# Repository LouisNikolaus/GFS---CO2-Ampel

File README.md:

# CO2-Ampel mit D1 mini (ESP8266)

Trägerplatine 100 × 60 mm (2 Lagen, nur THT-Bauteile) + 3D-gedrucktes Gehäuse 105 × 65 × 27 mm.

## Ordner

```
Platine/        KiCad-10-Projekt (CO2-Ampel.kicad_pro hier öffnen)
  lib/          Projektbibliothek: Symbol + Footprint D1 mini
  fertigung/    Gerber-ZIP, Stückliste, Layout-PDF, Renderings
  pruefberichte/  ERC/DRC-Berichte
  scripts/      Generatoren für Schaltplan, Platine und Router
gehaeuse/       STL-Dateien für den 3D-Druck
  scripts/      Gehäuse-Generator (parametrisch)
ESP-Code/       Firmware für den D1 mini (folgt)
```

| Datei | Inhalt |
|---|---|
| `Platine/CO2-Ampel_Schaltplan.pdf` | Schaltplan zum Ansehen ohne KiCad |
| `Platine/fertigung/CO2-Ampel_Gerber.zip` | Gerber + Bohrdaten für JLCPCB / Aisler / PCBWay |
| `Platine/fertigung/Stueckliste.csv` | Stückliste |
| `gehaeuse/Unterschale.stl`, `gehaeuse/Deckel.stl` | Druckdateien (Deckel liegt schon richtig herum) |

## Belegung D1 mini

| Pin | Funktion |
|---|---|
| D1 (GPIO5) | I2C SCL (Display + Sensor) |
| D2 (GPIO4) | I2C SDA |
| D3 (GPIO0) | Taster gegen GND (interner Pull-up) |
| D5 / D6 / D7 | LED rot / gelb / grün |
| D8 (GPIO15) | Summer über BC547 |
| 5V / 3V3 / G | Versorgung (über USB des D1 mini) |

## Zusätzlich zur Stückliste

- 2 × Buchsenleiste 1×8, RM 2,54 (für den D1 mini)
- 4 × Schraube M3 × 8 (Platine auf Abstandshalter, selbstschneidend)
- Aktiver Summer 5 V, 12 mm, Rastermaß 7,6 mm
- Taster 6 × 6 mm mit **13 mm Bauhöhe**

## Vor der Bestellung prüfen

1. **Pinfolge des CO2-Sensors**: J2 ist VCC–GND–SCL–SDA belegt. Das Sensormodul (SCD40/SCD41/SCD30 …) vergleichen.
2. **Pinfolge des OLED**: J1 ist GND–VCC–SCL–SDA belegt. Manche Displays haben VCC–GND!
3. **JP1** (Lötbrücke): ab Werk 3,3 V für den Sensor. Für 5 V die Brücke 1-2 auftrennen und 2-3 verbinden.
4. **R1/R2** nur bestücken, wenn weder Display noch Sensor eigene Pull-ups haben.

## Gehäuse

- Material: PETG oder PLA, 0,2 mm Schichthöhe, keine Stützstrukturen nötig.
- Unterschale mit der Öffnung nach oben drucken, den Deckel mit der Sichtseite aufs Druckbett.
- Der Deckel wird nur gesteckt (Klemmrand). Wenn er zu stramm sitzt, in `gehaeuse/scripts/gen_case.py` den Wert `LIP_CLEAR` erhöhen.
- Die **Trennwand** im Deckel sitzt über dem Schlitz in der Platine. Sie trennt den Sensor thermisch vom warmen ESP8266 und verbessert so die Temperaturmessung.
- **LEDs** erst einlöten, wenn der Deckel aufgesetzt ist. So stecken sie genau in den Löchern.
- **Wichtig:** Die Bauhöhe hängt davon ab, wie D1 mini und Display gesteckt sind. Maßgeblich ist der Parameter `PARTS_H` (Standard 16 mm über Platinenoberseite). Nachmessen und bei Bedarf anpassen:
  `python gehaeuse/scripts/gen_case.py`

## Neu erzeugen

Alle Befehle im Hauptordner ausführen (normales Python braucht `pip install manifold3d numpy`):

```
python Platine/scripts/gen_lib.py
python Platine/scripts/gen_sch.py
kicad-cli sch export netlist --format kicadsexpr -o Platine/CO2-Ampel.net Platine/CO2-Ampel.kicad_sch
"C:\Program Files\KiCad\10.0\bin\python.exe" Platine/scripts/gen_pcb.py
"C:\Program Files\KiCad\10.0\bin\python.exe" Platine/scripts/route_pcb.py
python gehaeuse/scripts/gen_case.py
```

Achtung: `gen_pcb.py` und `route_pcb.py` überschreiben die Platine. Wer das Layout von Hand in KiCad weiterbearbeitet, führt die Skripte danach nicht mehr aus.

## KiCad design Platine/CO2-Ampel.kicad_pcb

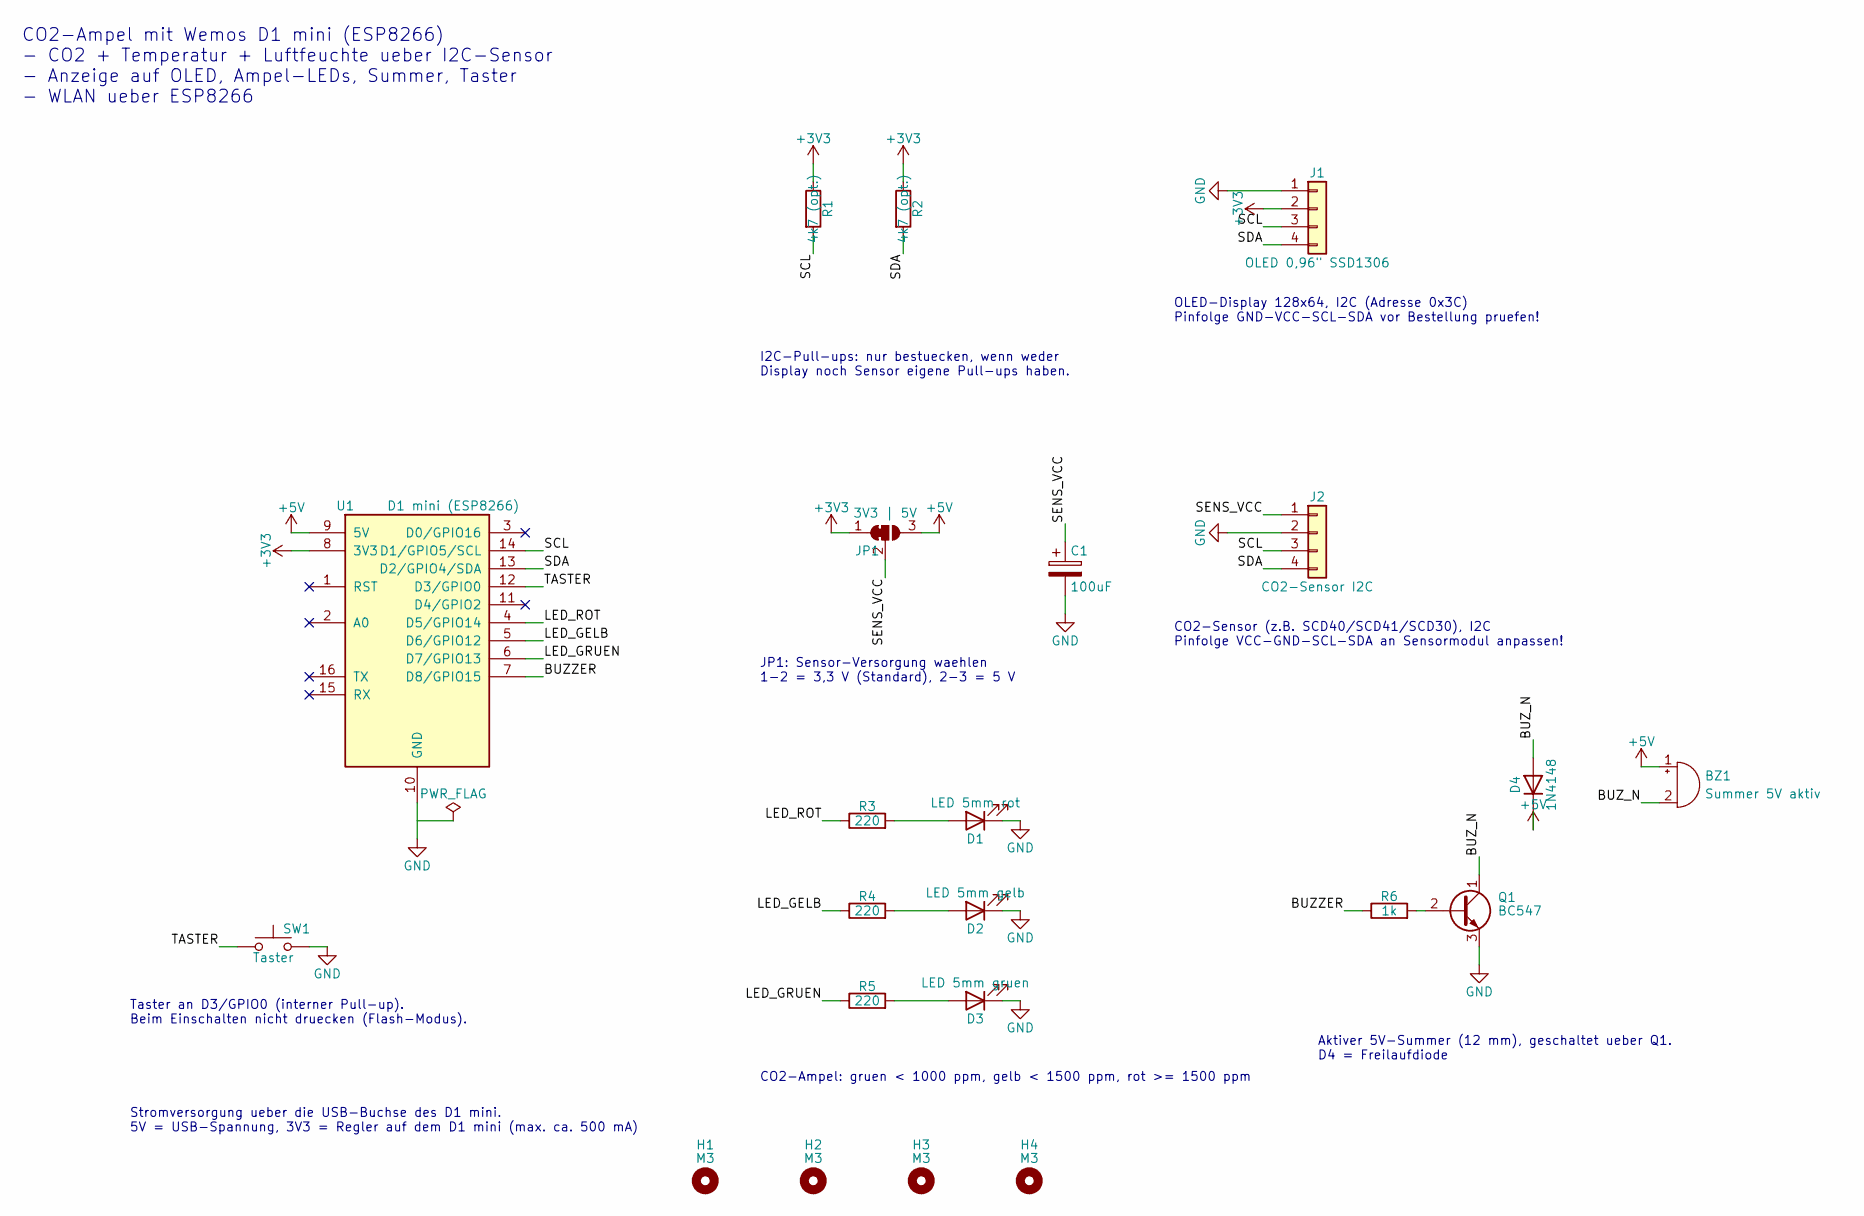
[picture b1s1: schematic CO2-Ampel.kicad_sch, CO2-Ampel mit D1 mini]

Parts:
BZ1: Summer 5V aktiv; Buzzer_12x9.5RM7.6
C1: 100uF; CP_Radial_D6.3mm_P2.50mm
D1: LED 5mm rot; LED_D5.0mm
D2: LED 5mm gelb; LED_D5.0mm
D3: LED 5mm gruen; LED_D5.0mm
D4: 1N4148; D_DO-35_SOD27_P7.62mm_Horizontal
H1, H2, H3, H4: M3; MountingHole_3.2mm_M3
J1: OLED 0,96" SSD1306; PinSocket_1x04_P2.54mm_Vertical
J2: CO2-Sensor I2C; PinSocket_1x04_P2.54mm_Vertical
JP1: 3V3 | 5V; SolderJumper-3_P1.3mm_Bridged12_RoundedPad1.0x1.5mm_NumberL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
Q1: BC547; TO-92_Inline
R1, R2: 4k7 (opt.); R_Axial_DIN0207_L6.3mm_D2.5mm_P7.62mm_Horizontal
R3, R4, R5: 220; R_Axial_DIN0207_L6.3mm_D2.5mm_P7.62mm_Horizontal
R6: 1k; R_Axial_DIN0207_L6.3mm_D2.5mm_P7.62mm_Horizontal
SW1: Taster; SW_PUSH_6mm_H13mm
U1: D1 mini (ESP8266); WEMOS_D1_mini

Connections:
+3V3: J1.2, JP1.1 (A), R1.1, R2.1, U1.8 (3V3)
+5V: BZ1.1 (+), D4.1 (K), JP1.3 (B), U1.9 (5V)
/BUZZER: R6.1, U1.7 (D8/GPIO15)
/BUZ_N: BZ1.2 (-), D4.2 (A), Q1.1 (C)
/LED_GELB: R4.1, U1.5 (D6/GPIO12)
/LED_GRUEN: R5.1, U1.6 (D7/GPIO13)
/LED_ROT: R3.1, U1.4 (D5/GPIO14)
/SCL: J1.3, J2.3, R1.2, U1.14 (D1/GPIO5/SCL)
/SDA: J1.4, J2.4, R2.2, U1.13 (D2/GPIO4/SDA)
/SENS_VCC: C1.1, J2.1, JP1.2 (C)
/TASTER: SW1.1, U1.12 (D3/GPIO0)
GND: C1.2, D1.1 (K), D2.1 (K), D3.1 (K), J1.1, J2.2, Q1.3 (E), SW1.2, U1.10 (GND)
unnamed: D1.2 (A), R3.2
unnamed: D2.2 (A), R4.2
unnamed: D3.2 (A), R5.2
unnamed: Q1.2 (B), R6.2

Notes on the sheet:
Stromversorgung ueber die USB-Buchse des D1 mini. 5V = USB-Spannung, 3V3 = Regler auf dem D1 mini (max. ca. 500 mA)
I2C-Pull-ups: nur bestuecken, wenn weder Display noch Sensor eigene Pull-ups haben.
OLED-Display 128x64, I2C (Adresse 0x3C) Pinfolge GND-VCC-SCL-SDA vor Bestellung pruefen!
CO2-Sensor (z.B. SCD40/SCD41/SCD30), I2C Pinfolge VCC-GND-SCL-SDA an Sensormodul anpassen!
JP1: Sensor-Versorgung waehlen 1-2 = 3,3 V (Standard), 2-3 = 5 V
CO2-Ampel: gruen < 1000 ppm, gelb < 1500 ppm, rot >= 1500 ppm
Aktiver 5V-Summer (12 mm), geschaltet ueber Q1. D4 = Freilaufdiode
Taster an D3/GPIO0 (interner Pull-up). Beim Einschalten nicht druecken (Flash-Modus).
CO2-Ampel mit Wemos D1 mini (ESP8266) - CO2 + Temperatur + Luftfeuchte ueber I2C-Sensor - Anzeige auf OLED, Ampel-LEDs, Summer, Taster - WLAN ueber ESP8266

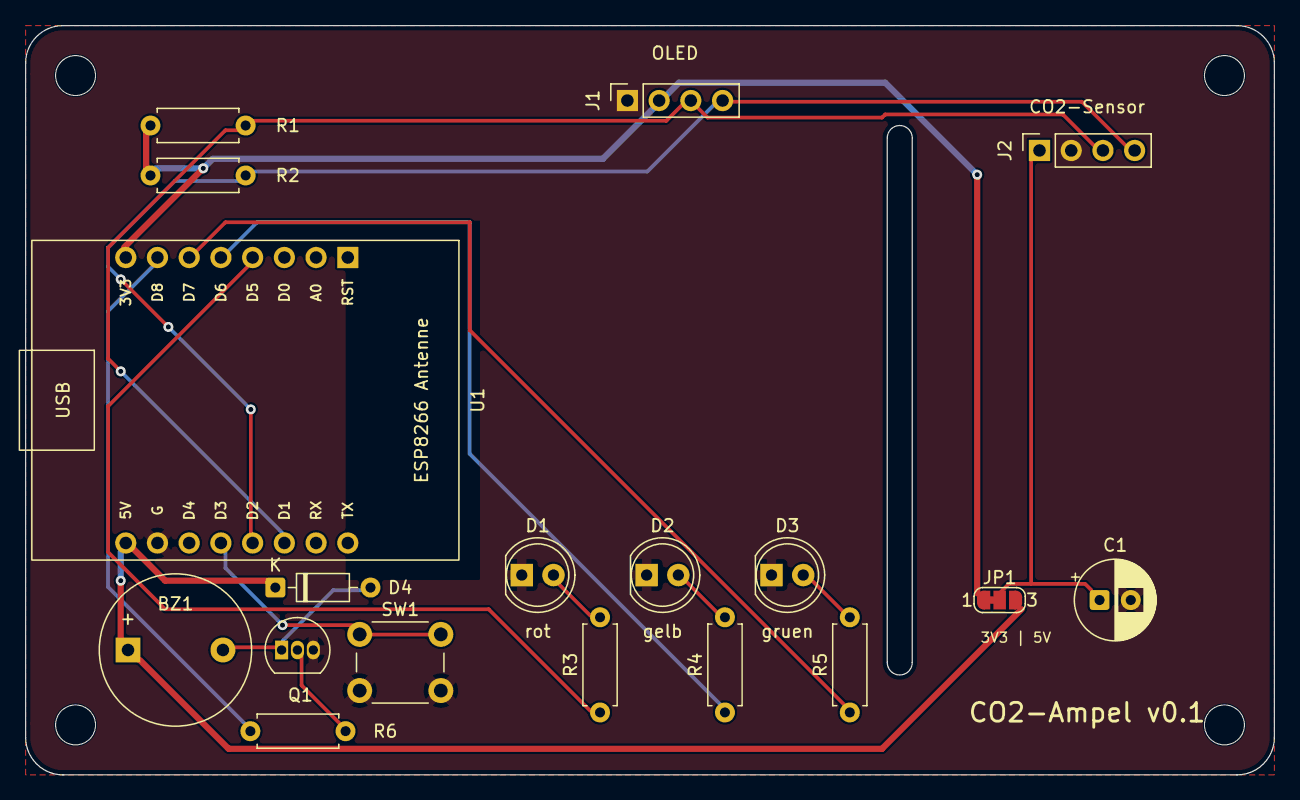
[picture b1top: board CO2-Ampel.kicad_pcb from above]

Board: 2 copper layers, 100.0 x 60.0 mm, 22 parts (0 on the bottom side), 16 nets.

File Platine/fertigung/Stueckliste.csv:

"Reference","Value","Footprint","QUANTITY"
"BZ1","Summer 5V aktiv","Buzzer_Beeper:Buzzer_12x9.5RM7.6","1"
"C1","100uF","Capacitor_THT:CP_Radial_D6.3mm_P2.50mm","1"
"D1","LED 5mm rot","LED_THT:LED_D5.0mm","1"
"D2","LED 5mm gelb","LED_THT:LED_D5.0mm","1"
"D3","LED 5mm gruen","LED_THT:LED_D5.0mm","1"
"D4","1N4148","Diode_THT:D_DO-35_SOD27_P7.62mm_Horizontal","1"
"J1","OLED 0,96"" SSD1306","Connector_PinSocket_2.54mm:PinSocket_1x04_P2.54mm_Vertical","1"
"J2","CO2-Sensor I2C","Connector_PinSocket_2.54mm:PinSocket_1x04_P2.54mm_Vertical","1"
"Q1","BC547","Package_TO_SOT_THT:TO-92_Inline","1"
"R1,R2","4k7 (opt.)","Resistor_THT:R_Axial_DIN0207_L6.3mm_D2.5mm_P7.62mm_Horizontal","2"
"R3-R5","220","Resistor_THT:R_Axial_DIN0207_L6.3mm_D2.5mm_P7.62mm_Horizontal","3"
"R6","1k","Resistor_THT:R_Axial_DIN0207_L6.3mm_D2.5mm_P7.62mm_Horizontal","1"
"SW1","Taster","Button_Switch_THT:SW_PUSH_6mm_H13mm","1"
"U1","D1 mini (ESP8266)","CO2:WEMOS_D1_mini","1"

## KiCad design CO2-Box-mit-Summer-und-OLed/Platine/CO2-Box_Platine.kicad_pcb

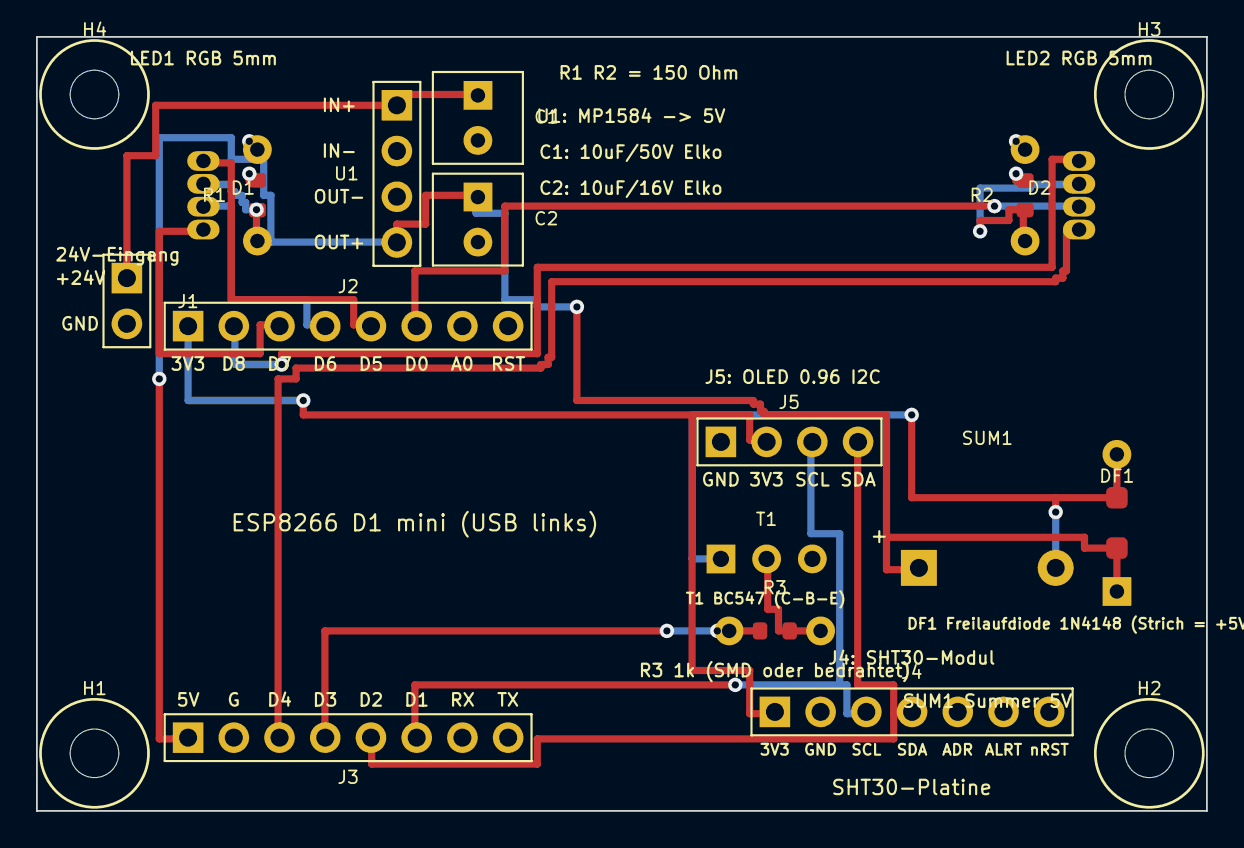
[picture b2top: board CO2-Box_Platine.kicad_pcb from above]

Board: 2 copper layers, 65.0 x 43.0 mm, 20 parts (0 on the bottom side), 17 nets.

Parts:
C1: 10u/50V Elko; CP_Radial_D5.0mm_P2.50mm
C2: 10u/16V Elko; CP_Radial_D5.0mm_P2.50mm
D1: RGB links; LED_D5.0mm-4_RGB
D2: RGB rechts; LED_D5.0mm-4_RGB
DF1: 1N4148 Freilauf; D_DO-35_SOD27_P7.62mm_Horizontal
H1, H2, H3, H4: M2.5; MountingHole_2.7mm_M2.5
J1: 24V IN; PinHeader_1x02_P2.54mm_Horizontal
J2: ESP hinten; PinSocket_1x08_P2.54mm_Vertical
J3: ESP vorn; PinSocket_1x08_P2.54mm_Vertical
J4: SHT30-Platine; PinHeader_1x07_P2.54mm_Vertical
J5: OLED I2C; PinHeader_1x04_P2.54mm_Vertical
R1, R2: 150; R_Axial_DIN0207_L6.3mm_P5.08mm
R3: 1k; R_Axial_DIN0207_L6.3mm_P5.08mm
SUM1: Summer aktiv 5V; Buzzer_12x9.5RM7.6
T1: BC547 NPN; TO-92_Inline_Wide
U1: MP1584-Modul (auf 5V einstellen); PinHeader_1x04_P2.54mm_Vertical

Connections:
+3V3: J2.1, J4.1, J5.2
+5V: C2.1, DF1.1, J3.1, SUM1.1, U1.4
+24V: C1.1, J1.1, U1.1
BZ_N: DF1.2, SUM1.2, T1.1
D0: D2.3, J2.6
D3: J3.4, R3.1
D4: D2.4, J3.3
D5: D1.1, J2.5
D6: D1.3, J2.4
D7: D1.4, J2.3
D8: D2.1, J2.2
GND: C1.2, C2.2, J1.2, J3.2, J4.2, J5.1, R1.2, R2.2, T1.3, U1.2, U1.3
L1_K: D1.2, R1.1
L2_K: D2.2, R2.1
Q1_B: R3.2, T1.2
SCL: J3.6, J4.3, J5.3
SDA: J3.5, J4.4, J5.4

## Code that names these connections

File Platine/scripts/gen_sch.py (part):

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    noconn(U1.pin(p)[:2])
label(U1.pin(14), "SCL")
label(U1.pin(13), "SDA")
label(U1.pin(12), "TASTER")
label(U1.pin(4), "LED_ROT")
label(U1.pin(5), "LED_GELB")
label(U1.pin(6), "LED_GRUEN")
label(U1.pin(7), "BUZZER")
gx, gy, _ = U1.pin(10)
wire((gx, gy), (gx, gy + 2.54), (gx + 5.08, gy + 2.54))
Part("#PWR_FLAG1", "power:PWR_FLAG", gx + 5.08, gy + 2.54, value="PWR_FLAG")
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
# ---------------------------------------------------------------- CO2-Sensor
J2 = Part("J2", "Connector_Generic:Conn_01x04", g(80), g(34), value="CO2-Sensor I2C", footprint=FP_SOCK4)
label(J2.pin(1), "SENS_VCC")
power(J2.pin(2), "GND", body="left", length=7.62)
label(J2.pin(3), "SCL")
label(J2.pin(4), "SDA")
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           footprint="Jumper:SolderJumper-3_P1.3mm_Bridged12_RoundedPad1.0x1.5mm_NumberLabels", in_bom=False)
power(JP1.pin(1), "+3V3", body="up")
power(JP1.pin(3), "+5V", body="up")
label(JP1.pin(2), "SENS_VCC")
C1 = Part("C1", "Device:C_Polarized", g(66), g(36), value="100uF",
          footprint="Capacitor_THT:CP_Radial_D6.3mm_P2.50mm")
label(C1.pin(1), "SENS_VCC")
power(C1.pin(2), "GND")
text("JP1: Sensor-Versorgung waehlen\n1-2 = 3,3 V (Standard), 2-3 = 5 V", g(49), g(41))

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# ---------------------------------------------------------------- Summer
R6 = Part("R6", "Device:R", g(84), g(55), angle=90, value="1k", footprint=FP_R)
Q1 = Part("Q1", "Transistor_BJT:BC547", g(84) + 3.81 + 5.08 + 1.27, g(55), value="BC547")
label(R6.pin(1), "BUZZER")
wire(R6.pin(2)[:2], Q1.pin(2)[:2])
power(Q1.pin(3), "GND", body="down")
label(Q1.pin(1), "BUZ_N")
BZ1 = Part("BZ1", "Device:Buzzer", g(100), g(48), value="Summer 5V aktiv",
           footprint="Buzzer_Beeper:Buzzer_12x9.5RM7.6")
power(BZ1.pin(1), "+5V", body="up")
label(BZ1.pin(2), "BUZ_N")
D4 = Part("D4", "Diode:1N4148", g(92), g(48), angle=90, value="1N4148")
power(D4.pin(1), "+5V", body="up")
label(D4.pin(2), "BUZ_N")
text("Aktiver 5V-Summer (12 mm), geschaltet ueber Q1.\nD4 = Freilaufdiode", g(80), g(62))

# ---------------------------------------------------------------- Taster
SW1 = Part("SW1", "Switch:SW_Push", g(22), g(57), value="Taster",
           footprint="Button_Switch_THT:SW_PUSH_6mm_H13mm")
label(SW1.pin(1), "TASTER")
power(SW1.pin(2), "GND", body="down")
text("Taster an D3/GPIO0 (interner Pull-up).\nBeim Einschalten nicht druecken (Flash-Modus).", g(14), g(60))

# ---------------------------------------------------------------- Befestigung
for i in range(4):
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
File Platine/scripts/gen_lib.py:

"""Erzeugt die Projektbibliothek: Symbol + Footprint fuer den Wemos/AZDelivery D1 mini."""
import os
import uuid

ROOT = os.path.dirname(os.path.dirname(os.path.abspath(__file__)))

# Nummer, Name, Seite, y-Position (Symbol), elektrischer Typ
# Nummerierung = Footprint-Pads: links 1..8 (RST..3V3, Antenne oben), rechts 9..16 (5V..TX)
D1_PINS = [
    (9, "5V", "L", 15.24, "power_out"),
    (8, "3V3", "L", 12.7, "power_out"),
    (1, "RST", "L", 7.62, "input"),
    (2, "A0", "L", 2.54, "input"),
    (16, "TX", "L", -5.08, "output"),
    (15, "RX", "L", -7.62, "input"),
    (3, "D0/GPIO16", "R", 15.24, "bidirectional"),
    (14, "D1/GPIO5/SCL", "R", 12.7, "bidirectional"),
    (13, "D2/GPIO4/SDA", "R", 10.16, "bidirectional"),
    (12, "D3/GPIO0", "R", 7.62, "bidirectional"),
    (11, "D4/GPIO2", "R", 5.08, "bidirectional"),
    (4, "D5/GPIO14", "R", 2.54, "bidirectional"),
    (5, "D6/GPIO12", "R", 0.0, "bidirectional"),
    (6, "D7/GPIO13", "R", -2.54, "bidirectional"),
    (7, "D8/GPIO15", "R", -5.08, "bidirectional"),
    (10, "GND", "B", 0.0, "power_in"),
]


def font(size=1.27, hide=False):
    return f'(effects (font (size {size} {size})){" (hide yes)" if hide else ""})'


def symbol_lib():
    pins = []
    for num, name, side, y, typ in D1_PINS:
        if side == "L":
            at = f"-15.24 {y} 0"
        elif side == "R":
            at = f"15.24 {y} 180"
        else:
            at = "0 -22.86 90"
        pins.append(
            f'(pin {typ} line (at {at}) (length 5.08) (name "{name}" {font()}) (number "{num}" {font()}))'
        )
    return f"""(kicad_symbol_lib (version 20241209) (generator "claude_gen") (generator_version "9.0")
  (symbol "WeMos_D1_mini" (pin_names (offset 1.016)) (exclude_from_sim no) (in_bom yes) (on_board yes)
    (property "Reference" "U" (at -10.16 19.05 0) {font()})
    (property "Value" "WeMos_D1_mini" (at 5.08 19.05 0) {font()})
    (property "Footprint" "CO2:WEMOS_D1_mini" (at 0 -26.67 0) {font(hide=True)})
    (property "Datasheet" "https://www.wemos.cc/en/latest/d1/d1_mini.html" (at 0 0 0) {font(hide=True)})
    (property "Description" "ESP8266 Modul D1 mini (AZDelivery / Wemos), steckbar" (at 0 0 0) {font(hide=True)})
    (symbol "WeMos_D1_mini_0_1"
      (rectangle (start -10.16 17.78) (end 10.16 -17.78) (stroke (width 0.254) (type default)) (fill (type background)))
    )
    (symbol "WeMos_D1_mini_1_1"
      {chr(10).join('      ' + p for p in pins)}
    )
  )
)
"""


def u():
    return str(uuid.uuid4())


def footprint():
    # Ursprung = Pad 1 (RST). Reihenabstand 22,86 mm (0.9"), Antenne oben (-y), USB unten (+y)
    x0, x1, y0, y1 = -1.37, 24.23, -8.9, 25.3
    items = []

    def line(a, b, layer, w):
        items.append(
            f'(fp_line (start {a[0]} {a[1]}) (end {b[0]} {b[1]}) (stroke (width {w}) (type solid)) (layer "{layer}") (uuid "{u()}"))'
        )

    def rect(a, b, layer, w):
        items.append(
            f'(fp_rect (start {a[0]} {a[1]}) (end {b[0]} {b[1]}) (stroke (width {w}) (type solid)) (fill no) (layer "{layer}") (uuid "{u()}"))'
        )

    def text(t, x, y, layer, size=1.0):
        items.append(
            f'(fp_text user "{t}" (at {x} {y} 0) (layer "{layer}") (uuid "{u()}") (effects (font (size {size} {size}) (thickness 0.15))))'
        )

    rect((x0, y0), (x1, y1), "F.SilkS", 0.12)
    rect((x0, y0), (x1, y1), "F.Fab", 0.1)
    rect((x0 - 0.5, y0 - 0.5), (x1 + 0.5, y1 + 2.0), "F.CrtYd", 0.05)
    # USB-Buchse (ragt ca. 1 mm ueber)
    rect((11.43 - 4.0, y1 - 5.0), (11.43 + 4.0, y1 + 1.0), "F.SilkS", 0.12)
    text("USB", 11.43, y1 - 2.5, "F.SilkS")
    text("ESP8266 Antenne", 11.43, y0 + 3.0, "F.SilkS")
    names_l = ["RST", "A0", "D0", "D5", "D6", "D7", "D8", "3V3"]
    names_r = ["TX", "RX", "D1", "D2", "D3", "D4", "G", "5V"]
    for i, n in enumerate(names_l):
        text(n, 2.8, i * 2.54, "F.SilkS", 0.8)
    for i, n in enumerate(names_r):
        text(n, 22.86 - 2.6, i * 2.54, "F.SilkS", 0.8)

    pads = []
    for i in range(8):
        shape = "rect" if i == 0 else "circle"
        pads.append((str(i + 1), shape, 0.0, i * 2.54))
        pads.append((str(16 - i), "circle", 22.86, i * 2.54))
    padtxt = [
        f'(pad "{n}" thru_hole {s} (at {x} {y}) (size 1.7 1.7) (drill 1.0) (layers "*.Cu" "*.Mask") (remove_unused_layers no) (uuid "{u()}"))'
        for n, s, x, y in pads
    ]
    return f"""(footprint "WEMOS_D1_mini" (version 20241229) (generator "claude_gen") (generator_version "9.0") (layer "F.Cu")
  (descr "Wemos / AZDelivery D1 mini (ESP8266), 2x8 Buchsenleisten 2,54 mm, Reihenabstand 22,86 mm")
  (tags "ESP8266 D1 mini Wemos")
  (property "Reference" "REF**" (at 11.43 {y0 - 1.5} 0) (layer "F.SilkS") (uuid "{u()}") (effects (font (size 1 1) (thickness 0.15))))
  (property "Value" "WeMos_D1_mini" (at 11.43 {y1 + 3.5} 0) (layer "F.Fab") (uuid "{u()}") (effects (font (size 1 1) (thickness 0.15))))
  (attr through_hole)
  {chr(10).join('  ' + i for i in items)}
  {chr(10).join('  ' + p for p in padtxt)}
  (embedded_fonts no)
)
"""


if __name__ == "__main__":
    lib = os.path.join(ROOT, "lib")
    os.makedirs(os.path.join(lib, "CO2.pretty"), exist_ok=True)
    with open(os.path.join(lib, "CO2.kicad_sym"), "w", encoding="utf-8") as f:
        f.write(symbol_lib())
    with open(os.path.join(lib, "CO2.pretty", "WEMOS_D1_mini.kicad_mod"), "w", encoding="utf-8") as f:
        f.write(footprint())
    with open(os.path.join(ROOT, "sym-lib-table"), "w") as f:
        f.write('(sym_lib_table\n  (version 7)\n  (lib (name "CO2")(type "KiCad")(uri "${KIPRJMOD}/lib/CO2.kicad_sym")(options "")(descr "Projektbibliothek CO2-Ampel"))\n)\n')
    with open(os.path.join(ROOT, "fp-lib-table"), "w") as f:
        f.write('(fp_lib_table\n  (version 7)\n  (lib (name "CO2")(type "KiCad")(uri "${KIPRJMOD}/lib/CO2.pretty")(options "")(descr "Projektbibliothek CO2-Ampel"))\n)\n')
    print("Bibliothek erzeugt")
